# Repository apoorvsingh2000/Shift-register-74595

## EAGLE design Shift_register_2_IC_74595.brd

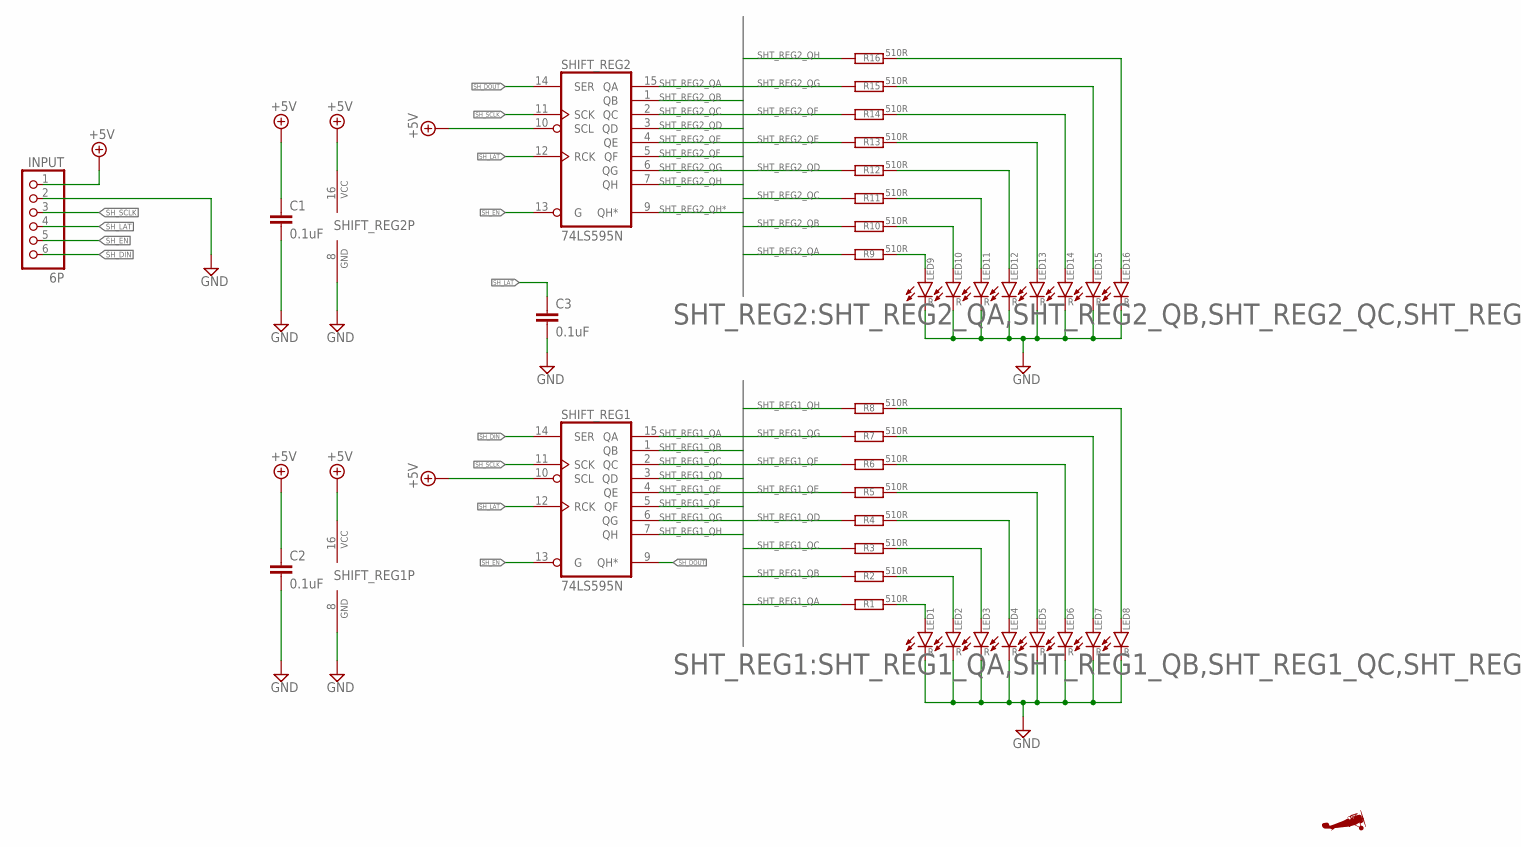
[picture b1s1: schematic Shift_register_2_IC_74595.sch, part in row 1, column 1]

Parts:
C1, C2, C3: 0.1uF; C050-030X075
INPUT: 6P; 1X06/90
LED1, LED2, LED3, LED4, LED5, LED6, LED7, LED8, LED9, LED10, LED11, LED12, LED13, LED14, LED15, LED16: R; LED5MM
R1, R2, R3, R4, R5, R6, R7, R8, R9, R10, R11, R12, R13, R14, R15, R16: 510R; 0207/10
SHIFT_REG1, SHIFT_REG2: 74LS595N; DIL16
U$1: AIRPLANE; AIRPLANE_MEDIUM

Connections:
+5V: C1.1, C2.1, INPUT.1, SHIFT_REG1.10 (SCL), SHIFT_REG1.16 (VCC), SHIFT_REG2.10 (SCL), SHIFT_REG2.16 (VCC)
GND: C1.2, C2.2, C3.2, INPUT.2, LED1.K (C), LED2.K (C), LED3.K (C), LED4.K (C), LED5.K (C), LED6.K (C), LED7.K (C), LED8.K (C), LED9.K (C), LED10.K (C), LED11.K (C), LED12.K (C), LED13.K (C), LED14.K (C), LED15.K (C), LED16.K (C), SHIFT_REG1.8 (GND), SHIFT_REG2.8 (GND)
unnamed: LED1.A, R1.2
unnamed: LED2.A, R2.2
unnamed: LED3.A, R3.2
unnamed: LED4.A, R4.2
unnamed: LED5.A, R5.2
unnamed: LED6.A, R6.2
unnamed: LED7.A, R7.2
unnamed: LED8.A, R8.2
unnamed: LED9.A, R9.2
unnamed: LED10.A, R10.2
unnamed: LED11.A, R11.2
unnamed: LED12.A, R12.2
unnamed: LED13.A, R13.2
unnamed: LED14.A, R14.2
unnamed: LED15.A, R15.2
unnamed: LED16.A, R16.2
SHT_REG1_QA: R1.1, SHIFT_REG1.15 (QA)
SHT_REG1_QB: R2.1, SHIFT_REG1.1 (QB)
SHT_REG1_QC: R3.1, SHIFT_REG1.2 (QC)
SHT_REG1_QD: R4.1, SHIFT_REG1.3 (QD)
SHT_REG1_QE: R5.1, SHIFT_REG1.4 (QE)
SHT_REG1_QF: R6.1, SHIFT_REG1.5 (QF)
SHT_REG1_QG: R7.1, SHIFT_REG1.6 (QG)
SHT_REG1_QH: R8.1, SHIFT_REG1.7 (QH)
SHT_REG2_QA: R9.1, SHIFT_REG2.15 (QA)
SHT_REG2_QB: R10.1, SHIFT_REG2.1 (QB)
SHT_REG2_QC: R11.1, SHIFT_REG2.2 (QC)
SHT_REG2_QD: R12.1, SHIFT_REG2.3 (QD)
SHT_REG2_QE: R13.1, SHIFT_REG2.4 (QE)
SHT_REG2_QF: R14.1, SHIFT_REG2.5 (QF)
SHT_REG2_QG: R15.1, SHIFT_REG2.6 (QG)
SHT_REG2_QH: R16.1, SHIFT_REG2.7 (QH)
SHT_REG2_QH*: SHIFT_REG2.9 (QH*)
SH_DIN: INPUT.6, SHIFT_REG1.14 (SER)
SH_DOUT: SHIFT_REG1.9 (QH*), SHIFT_REG2.14 (SER)
SH_EN: INPUT.5, SHIFT_REG1.13 (G), SHIFT_REG2.13 (G)
SH_LAT: C3.1, INPUT.4, SHIFT_REG1.12 (RCK), SHIFT_REG2.12 (RCK)
SH_SCLK: INPUT.3, SHIFT_REG1.11 (SCK), SHIFT_REG2.11 (SCK)

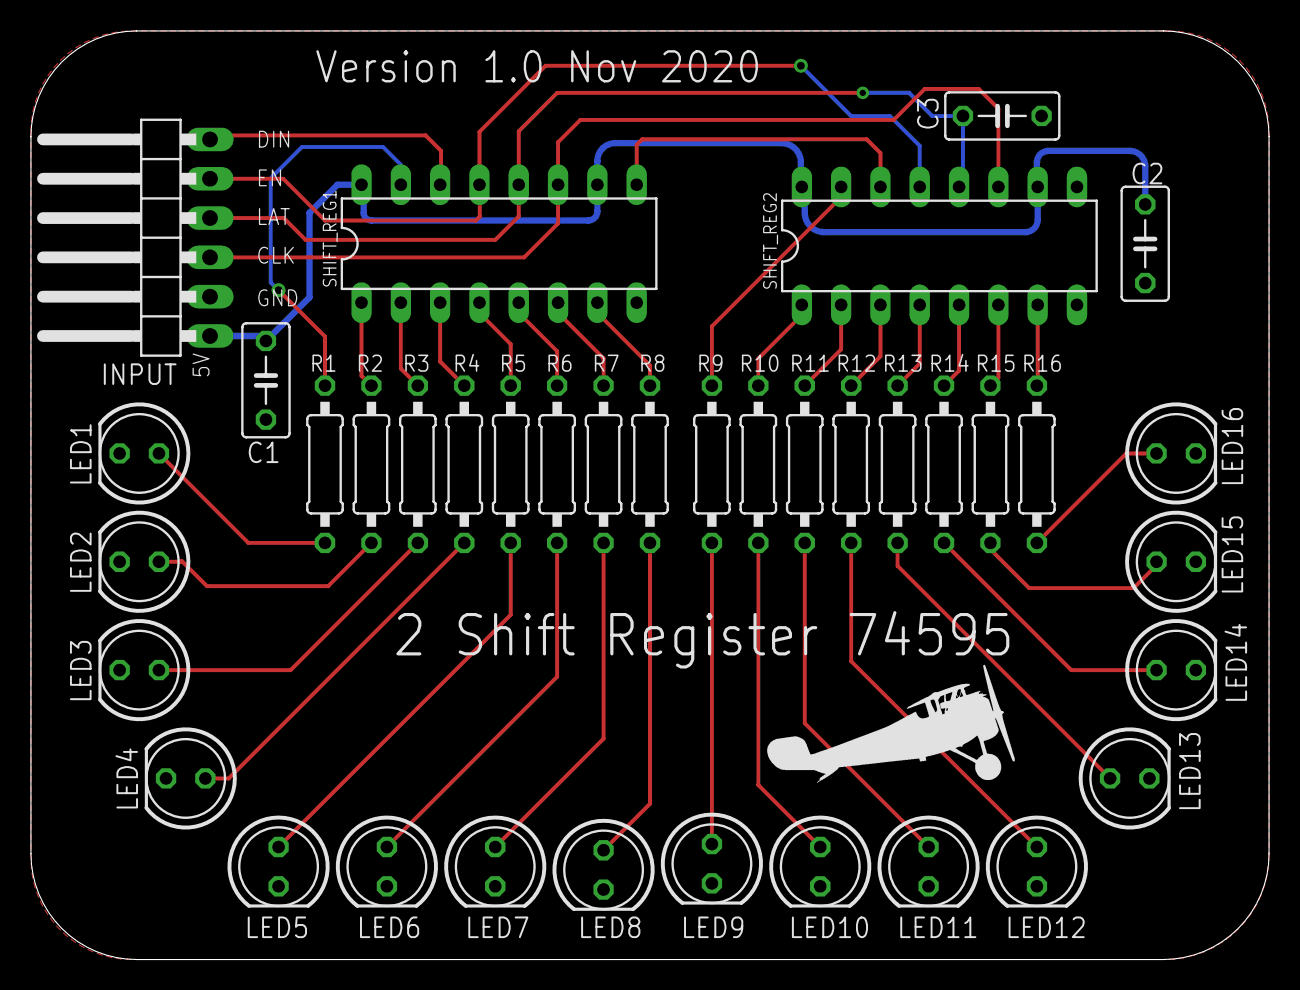
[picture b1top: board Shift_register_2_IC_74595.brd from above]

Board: 2 copper layers, 80.0 x 60.0 mm, 39 parts (0 on the bottom side), 39 nets.

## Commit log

2021-05-04 🎭shift reg
